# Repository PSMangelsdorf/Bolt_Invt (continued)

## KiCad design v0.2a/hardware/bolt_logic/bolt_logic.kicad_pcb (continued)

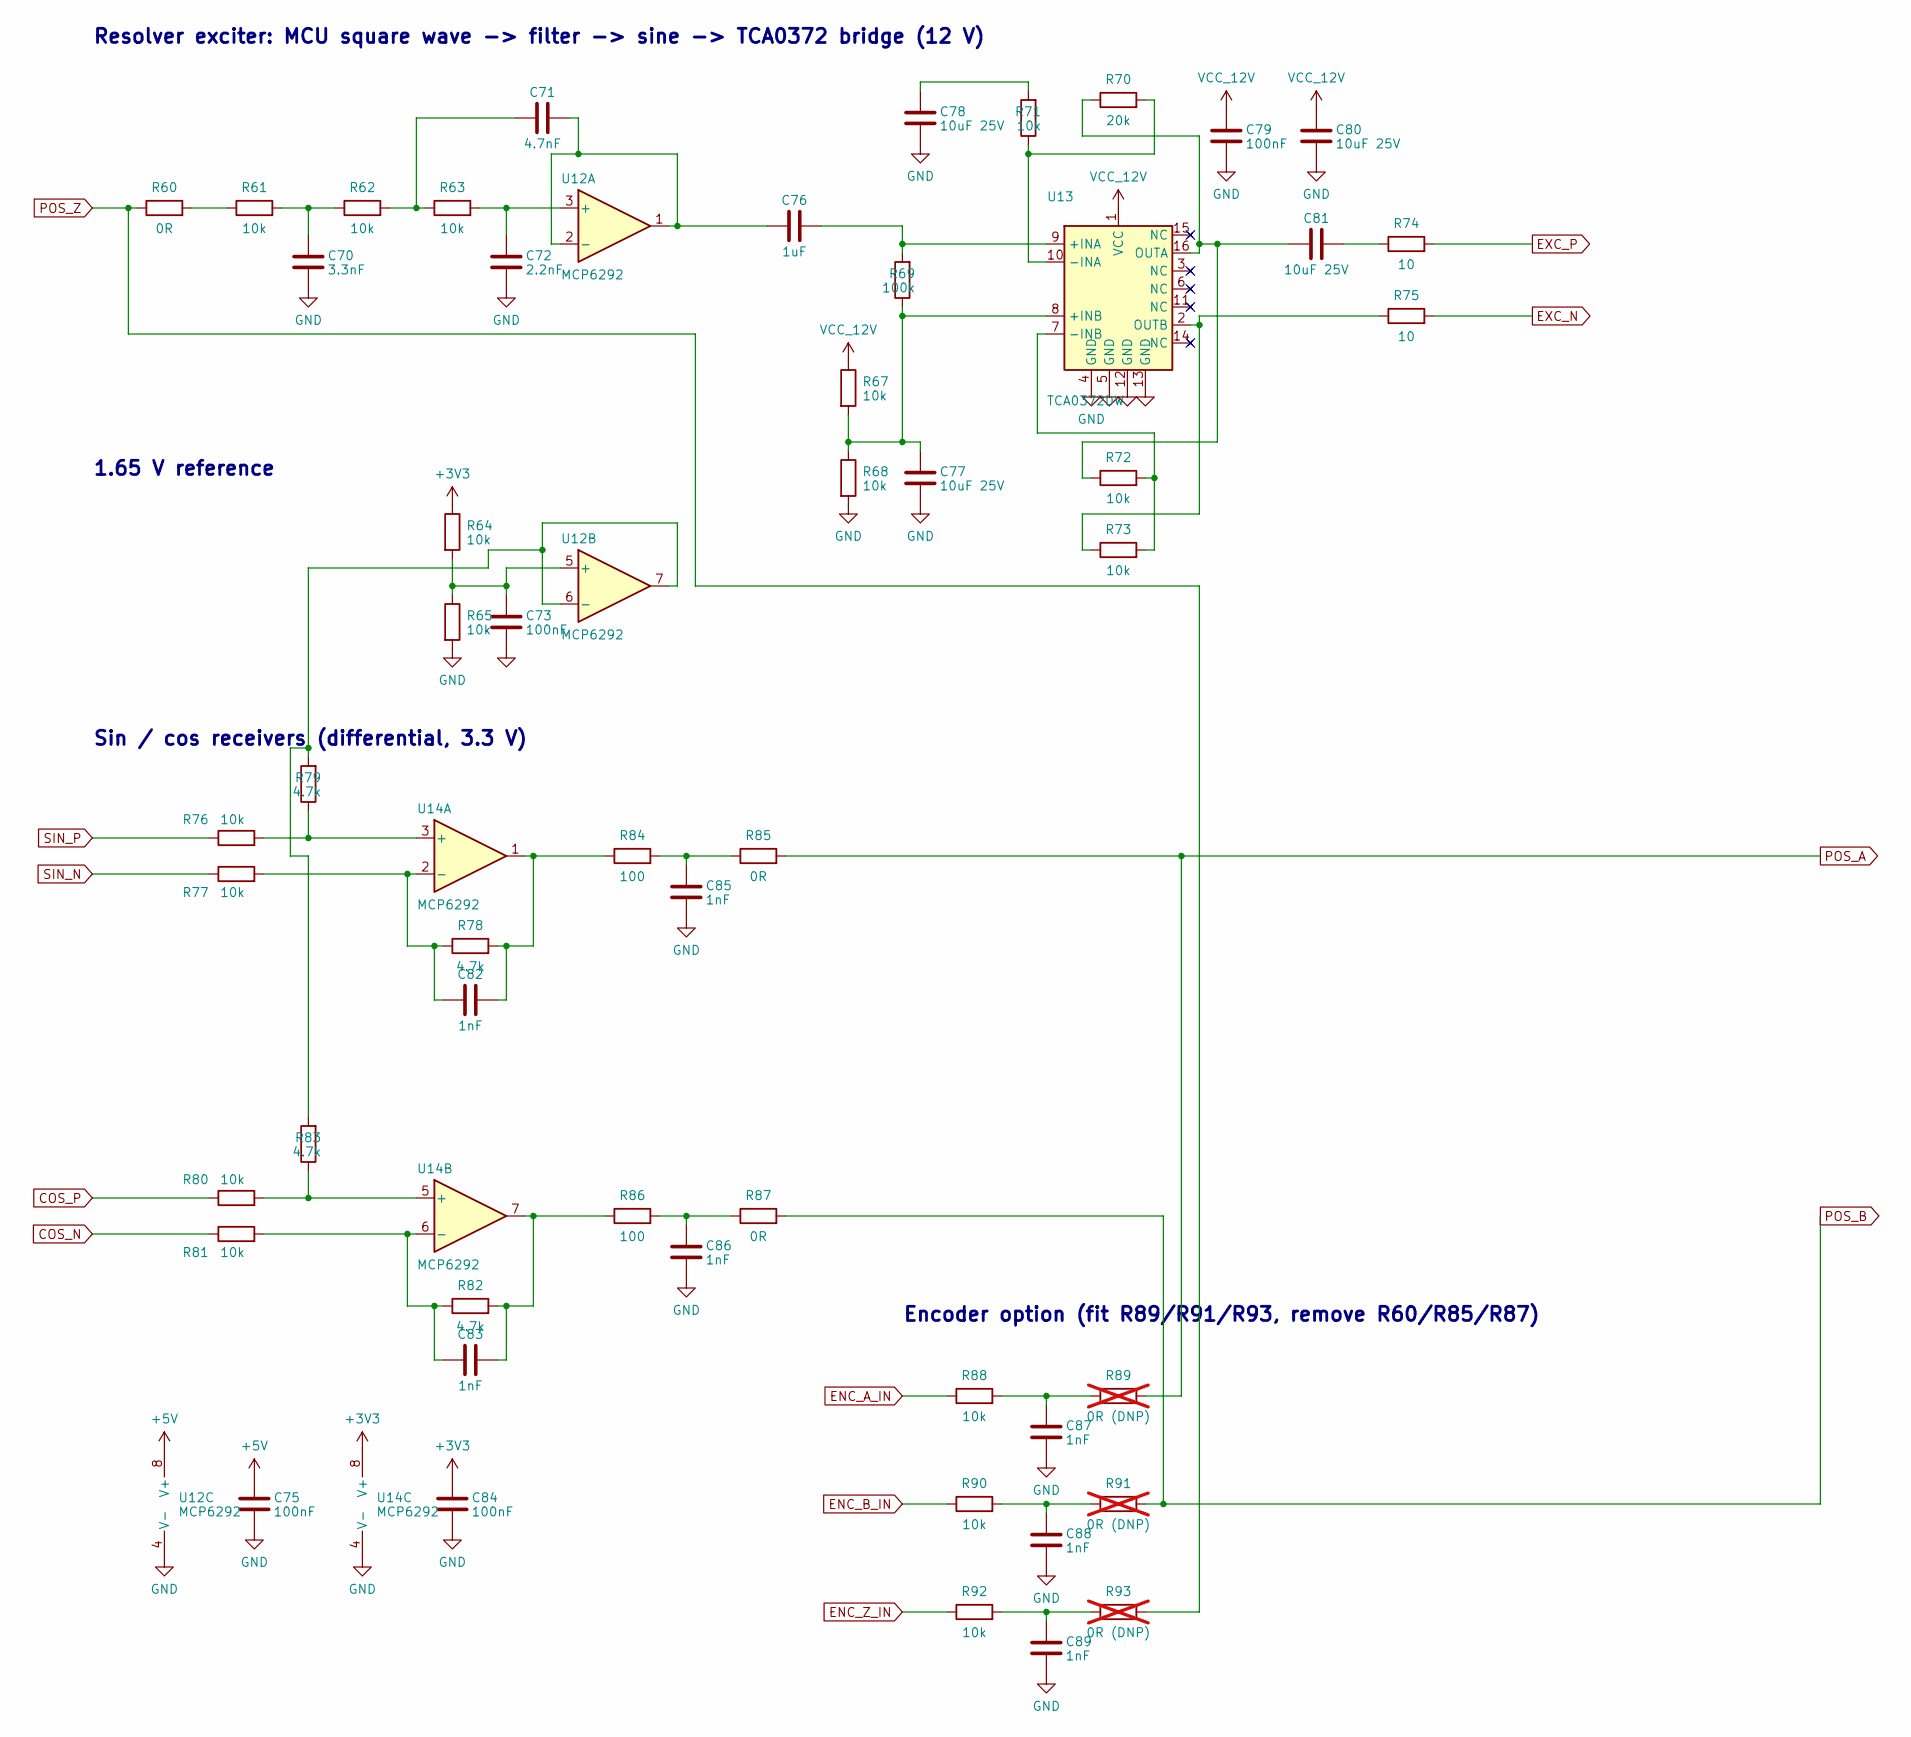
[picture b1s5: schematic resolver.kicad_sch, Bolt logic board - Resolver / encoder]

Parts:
C70: 3.3nF; C_0805_2012Metric
C71: 4.7nF; C_0805_2012Metric
C72: 2.2nF; C_0805_2012Metric
C73, C75, C79, C84: 100nF; C_0805_2012Metric
C76: 1uF; C_0805_2012Metric
C77, C78, C80, C81: 10uF 25V; C_1206_3216Metric
C82, C83, C85, C86, C87, C88, C89: 1nF; C_0805_2012Metric
R60, R85, R87: 0R; R_0805_2012Metric
R61, R62, R63, R64, R65, R67, R68, R71, R72, R73, R76, R77, R80, R81, R88, R90, R92: 10k; R_0805_2012Metric
R69: 100k; R_0805_2012Metric
R70: 20k; R_0805_2012Metric
R74, R75: 10; R_1206_3216Metric
R78, R79, R82, R83: 4.7k; R_0805_2012Metric
R84, R86: 100; R_0805_2012Metric
R89, R91, R93: 0R (DNP); R_0805_2012Metric; not fitted
U12, U14: MCP6292; SOIC-8_3.9x4.9mm_P1.27mm
U13: TCA0372DW; SOIC-16W_7.5x10.3mm_P1.27mm

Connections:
+3V3: C84.1, R64.1, U14.8 (V+); also elsewhere on the board
+5V: C75.1, U12.8 (V+); also elsewhere on the board
COS_INN: C83.1, R81.2, R82.1, U14.6 (-)
COS_INP: R80.2, R83.1, U14.5 (+)
COS_N: R81.1; also elsewhere on the board
COS_P: R80.1; also elsewhere on the board
ENC_A_F: C87.1, R88.2, R89.1
ENC_A_IN: R88.1; also elsewhere on the board
ENC_B_F: C88.1, R90.2, R91.1
ENC_B_IN: R90.1; also elsewhere on the board
ENC_Z_F: C89.1, R92.2, R93.1
ENC_Z_IN: R92.1; also elsewhere on the board
EXC_AC: C76.2, R69.2, U13.9 (+INA)
EXC_F1: C70.1, R61.2, R62.1
EXC_FBA: R70.2, R71.1, U13.10 (-INA)
EXC_FBB: R72.2, R73.2, U13.7 (-INB)
EXC_N: R75.2; also elsewhere on the board
EXC_OA: C81.1, R70.1, R72.1, U13.16 (OUTA)
EXC_OA_C: C81.2, R74.1
EXC_OB: R73.1, R75.1, U13.2 (OUTB)
EXC_P: R74.2; also elsewhere on the board
EXC_RGA: C78.1, R71.2
EXC_SIN: C71.2, C76.1, U12.1, U12.2 (-)
EXC_SK1: C71.1, R62.2, R63.1
EXC_SK2: C72.1, R63.2, U12.3 (+)
EXC_SQ: R60.2, R61.1
EXC_VB: C77.1, R67.2, R68.1, R69.1, U13.8 (+INB)
GND: C70.2, C72.2, C73.2, C75.2, C77.2, C78.2, C79.2, C80.2, C84.2, C85.2, C86.2, C87.2, C88.2, C89.2, R65.2, R68.2, U12.4 (V-), U13.4 (GND), U13.5 (GND), U13.12 (GND), U13.13 (GND), U14.4 (V-); also elsewhere on the board
POS_A: R85.2, R89.2; also elsewhere on the board
POS_B: R87.2, R91.2; also elsewhere on the board
POS_Z: R60.1, R93.2; also elsewhere on the board
RES_COS: C83.2, R82.2, R86.1, U14.7
RES_COS_F: C86.1, R86.2, R87.1
RES_SIN: C82.2, R78.2, R84.1, U14.1
RES_SIN_F: C85.1, R84.2, R85.1
SIN_INN: C82.1, R77.2, R78.1, U14.2 (-)
SIN_INP: R76.2, R79.1, U14.3 (+)
SIN_N: R77.1; also elsewhere on the board
SIN_P: R76.1; also elsewhere on the board
VCC_12V: C79.1, C80.1, R67.1, U13.1 (VCC); also elsewhere on the board
VREF_1V65: R79.2, R83.2, U12.6 (-), U12.7
VREF_DIV: C73.1, R64.2, R65.1, U12.5 (+)

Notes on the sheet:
Resolver exciter: MCU square wave -> filter -> sine -> TCA0372 bridge (12 V)
1.65 V reference
Sin / cos receivers (differential, 3.3 V)
Encoder option (fit R89/R91/R93, remove R60/R85/R87)

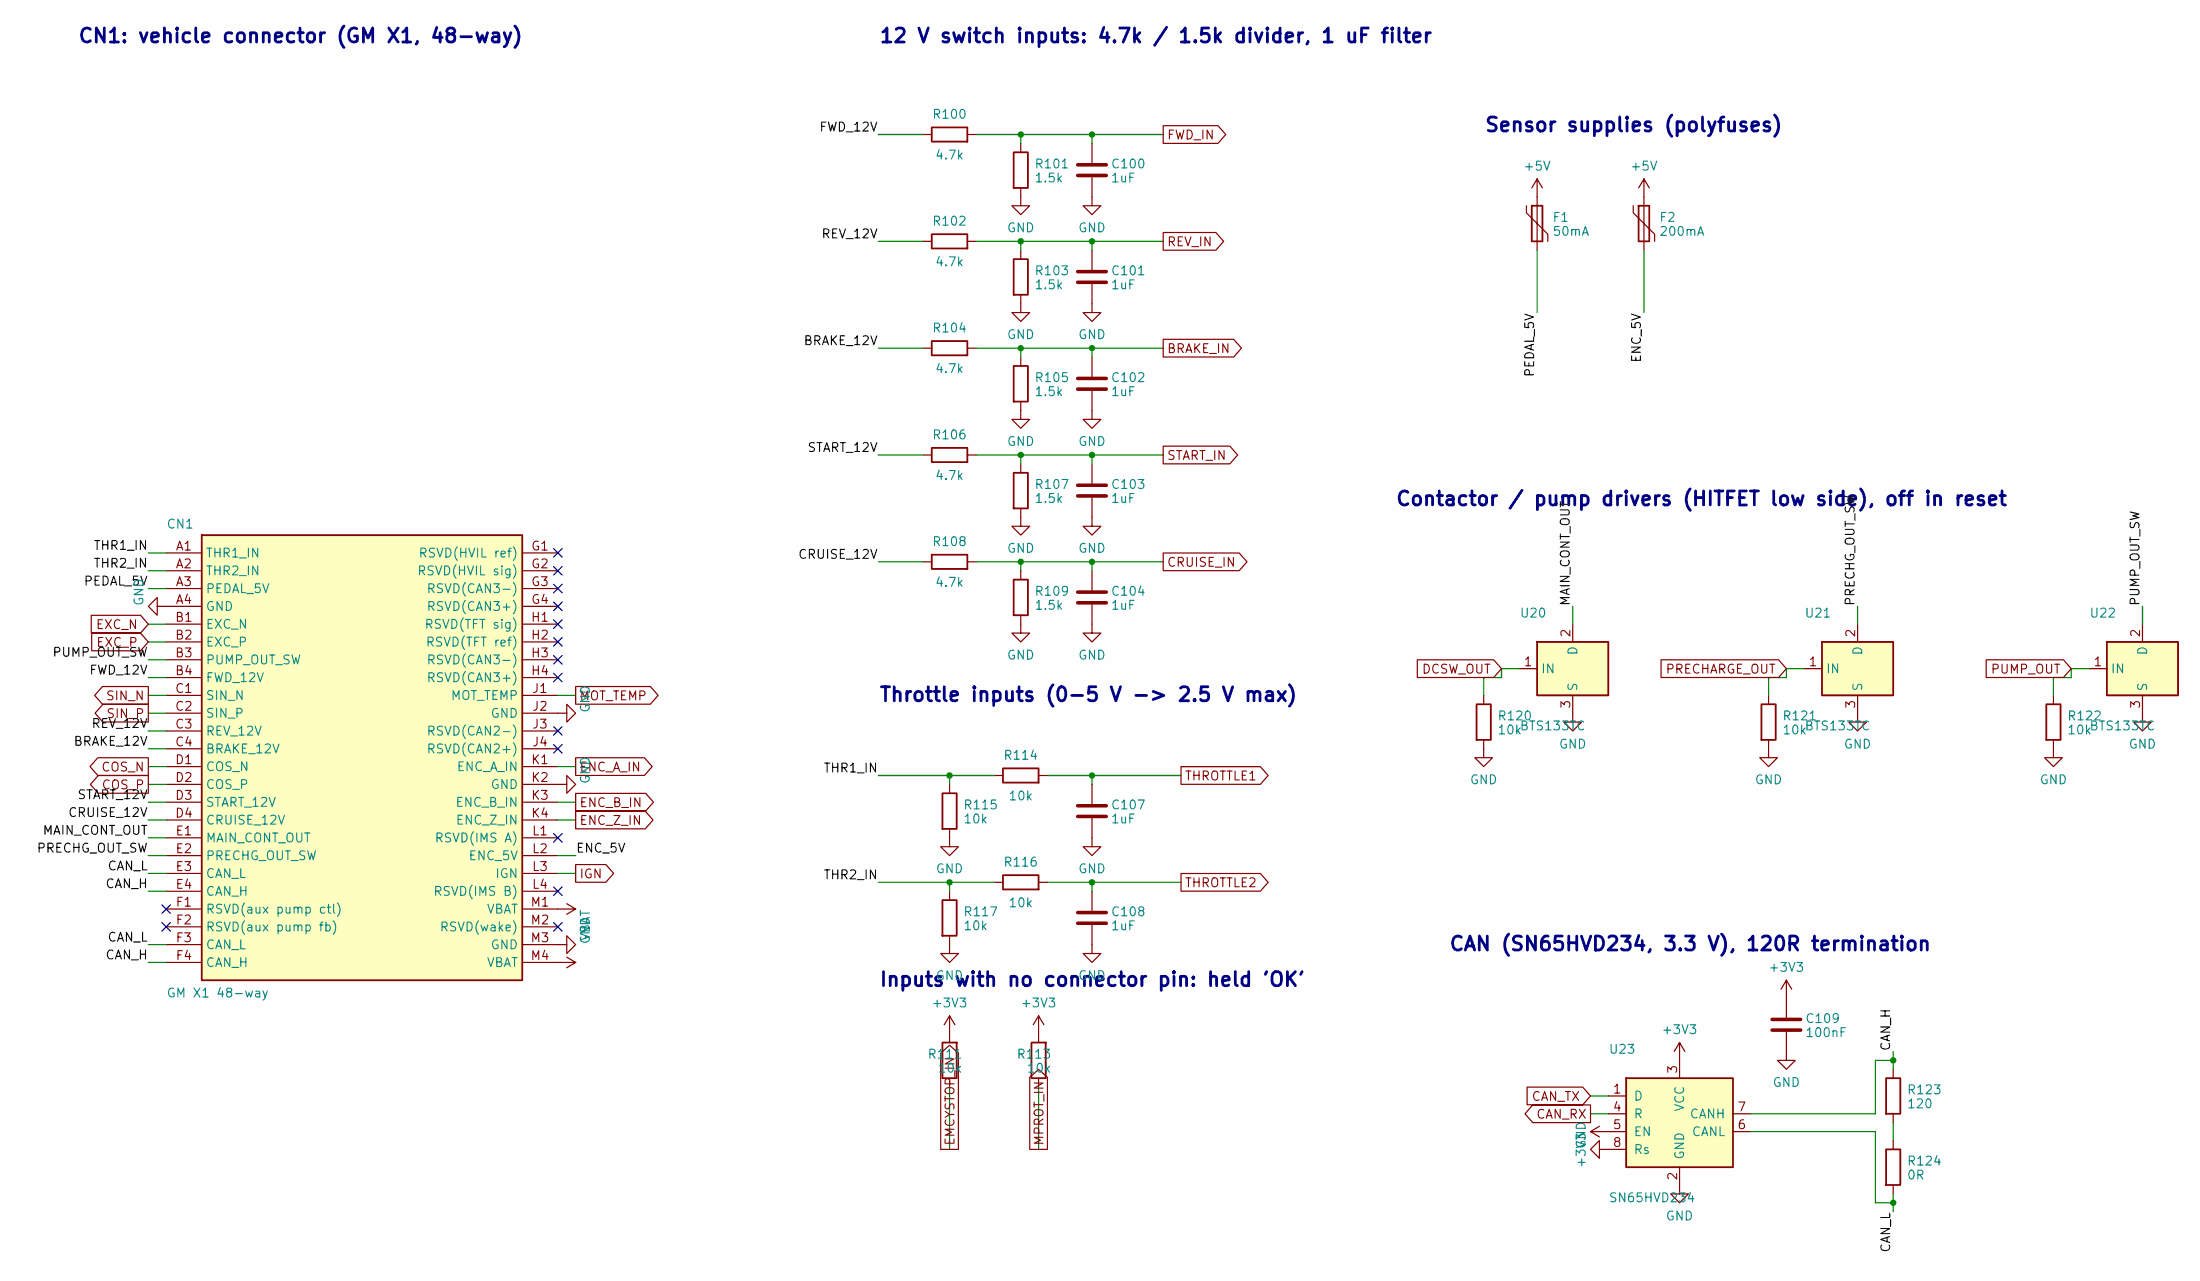
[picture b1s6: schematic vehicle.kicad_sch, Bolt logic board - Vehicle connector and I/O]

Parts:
C100, C101, C102, C103, C104, C107, C108: 1uF; C_0805_2012Metric
C109: 100nF; C_0805_2012Metric
CN1: GM X1 48-way; CN1_GM_48pos_4x12
F1: 50mA; Fuse_1206_3216Metric
F2: 200mA; Fuse_1206_3216Metric
R100, R102, R104, R106, R108: 4.7k; R_0805_2012Metric
R101, R103, R105, R107, R109: 1.5k; R_0805_2012Metric
R111, R113, R114, R115, R116, R117, R120, R121, R122: 10k; R_0805_2012Metric
R123: 120; R_0805_2012Metric
R124: 0R; R_0805_2012Metric
U20, U21, U22: BTS133TC; TO-263-2
U23: SN65HVD234; SOIC-8_3.9x4.9mm_P1.27mm

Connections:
+3V3: C109.1, R111.2, R113.2, U23.3 (VCC), U23.5 (EN); also elsewhere on the board
+5V: F1.1, F2.1; also elsewhere on the board
BRAKE_12V: CN1.C4 (BRAKE_12V), R104.1
BRAKE_IN: C102.1, R104.2, R105.1; also elsewhere on the board
CAN_H: CN1.E4 (CAN_H), CN1.F4 (CAN_H), R123.1, U23.7 (CANH)
CAN_L: CN1.E3 (CAN_L), CN1.F3 (CAN_L), R124.2, U23.6 (CANL)
CAN_RX: U23.4 (R); also elsewhere on the board
CAN_TERM: R123.2, R124.1
CAN_TX: U23.1 (D); also elsewhere on the board
COS_N: CN1.D1 (COS_N); also elsewhere on the board
COS_P: CN1.D2 (COS_P); also elsewhere on the board
CRUISE_12V: CN1.D4 (CRUISE_12V), R108.1
CRUISE_IN: C104.1, R108.2, R109.1; also elsewhere on the board
DCSW_OUT: R120.1, U20.1 (IN); also elsewhere on the board
EMCYSTOP_IN: R111.1; also elsewhere on the board
ENC_5V: CN1.L2 (ENC_5V), F2.2
ENC_A_IN: CN1.K1 (ENC_A_IN); also elsewhere on the board
ENC_B_IN: CN1.K3 (ENC_B_IN); also elsewhere on the board
ENC_Z_IN: CN1.K4 (ENC_Z_IN); also elsewhere on the board
EXC_N: CN1.B1 (EXC_N); also elsewhere on the board
EXC_P: CN1.B2 (EXC_P); also elsewhere on the board
FWD_12V: CN1.B4 (FWD_12V), R100.1
FWD_IN: C100.1, R100.2, R101.1; also elsewhere on the board
GND: C100.2, C101.2, C102.2, C103.2, C104.2, C107.2, C108.2, C109.2, CN1.A4 (GND), CN1.J2 (GND), CN1.K2 (GND), CN1.M3 (GND), R101.2, R103.2, R105.2, R107.2, R109.2, R115.2, R117.2, R120.2, R121.2, R122.2, U20.3 (S), U21.3 (S), U22.3 (S), U23.2 (GND), U23.8 (Rs); also elsewhere on the board
IGN: CN1.L3 (IGN); also elsewhere on the board
MAIN_CONT_OUT: CN1.E1 (MAIN_CONT_OUT), U20.2 (D)
MOT_TEMP: CN1.J1 (MOT_TEMP); also elsewhere on the board
MPROT_IN: R113.1; also elsewhere on the board
PEDAL_5V: CN1.A3 (PEDAL_5V), F1.2
PRECHARGE_OUT: R121.1, U21.1 (IN); also elsewhere on the board
PRECHG_OUT_SW: CN1.E2 (PRECHG_OUT_SW), U21.2 (D)
PUMP_OUT: R122.1, U22.1 (IN); also elsewhere on the board
PUMP_OUT_SW: CN1.B3 (PUMP_OUT_SW), U22.2 (D)
REV_12V: CN1.C3 (REV_12V), R102.1
REV_IN: C101.1, R102.2, R103.1; also elsewhere on the board
SIN_N: CN1.C1 (SIN_N); also elsewhere on the board
SIN_P: CN1.C2 (SIN_P); also elsewhere on the board
START_12V: CN1.D3 (START_12V), R106.1
START_IN: C103.1, R106.2, R107.1; also elsewhere on the board
THR1_IN: CN1.A1 (THR1_IN), R114.1, R115.1
THR2_IN: CN1.A2 (THR2_IN), R116.1, R117.1
THROTTLE1: C107.1, R114.2; also elsewhere on the board
THROTTLE2: C108.1, R116.2; also elsewhere on the board
VBAT: CN1.M1 (VBAT), CN1.M4 (VBAT); also elsewhere on the board

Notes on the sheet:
CN1: vehicle connector (GM X1, 48-way)
12 V switch inputs: 4.7k / 1.5k divider, 1 uF filter
Throttle inputs (0-5 V -> 2.5 V max)
Inputs with no connector pin: held 'OK'
Sensor supplies (polyfuses)
Contactor / pump drivers (HITFET low side), off in reset
CAN (SN65HVD234, 3.3 V), 120R termination

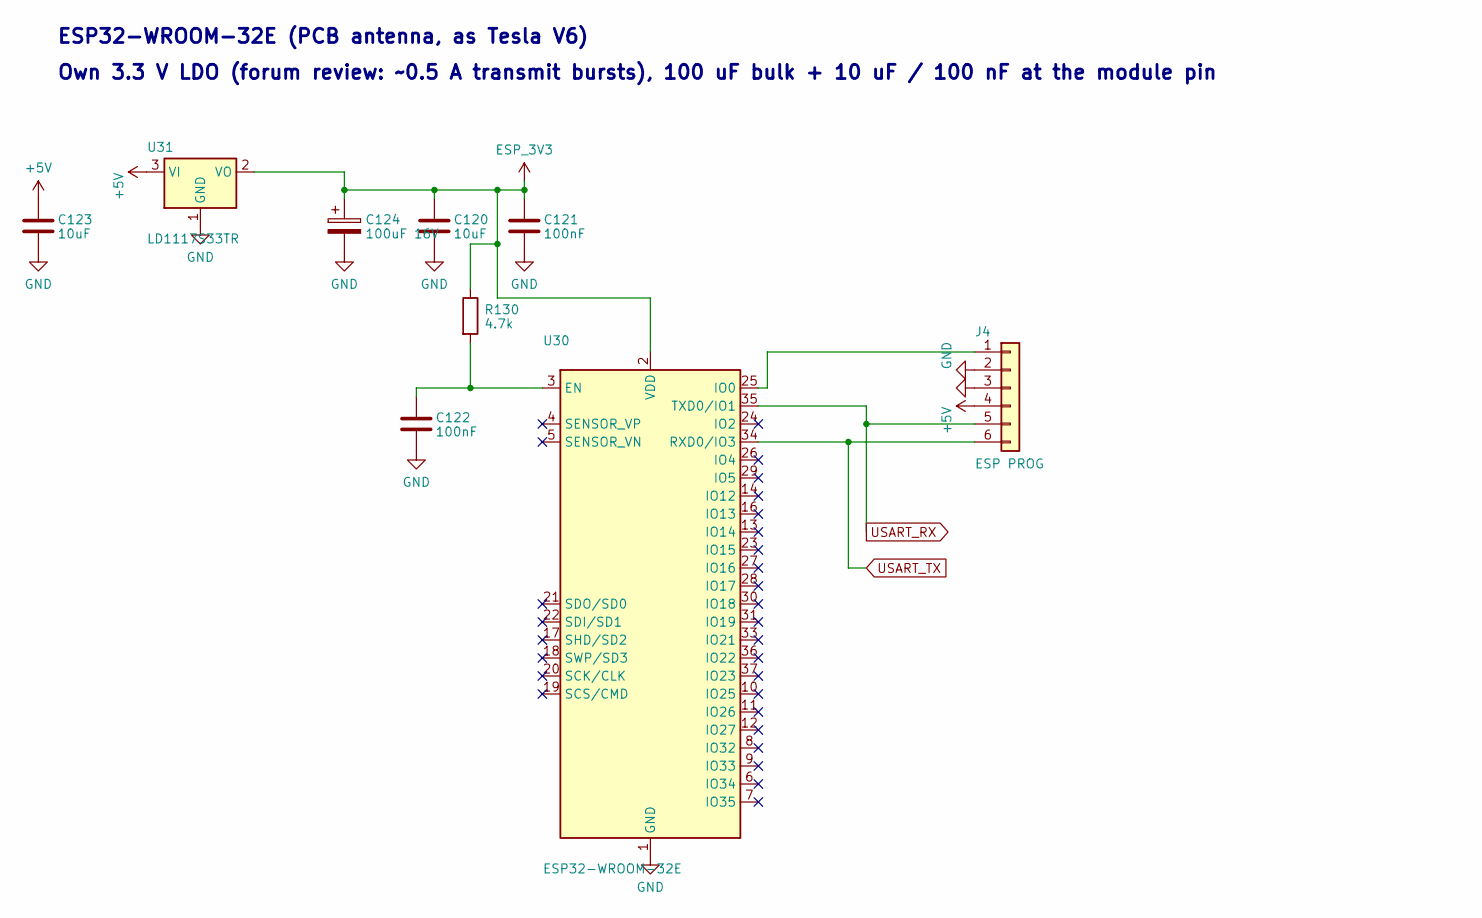
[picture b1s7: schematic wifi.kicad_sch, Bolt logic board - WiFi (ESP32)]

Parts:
C120, C123: 10uF; C_1206_3216Metric
C121, C122: 100nF; C_0805_2012Metric
C124: 100uF 16V; CP_Elec_6.3x5.4
J4: ESP PROG; PinHeader_1x06_P2.54mm_Vertical
R130: 4.7k; R_0805_2012Metric
U30: ESP32-WROOM-32E; ESP32-WROOM-32
U31: LD1117S33TR; SOT-223-3_TabPin2

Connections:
+5V: C123.1, J4.4, U31.3 (VI); also elsewhere on the board
ESP_3V3: C120.1, C121.1, C124.1, R130.1, U30.2 (VDD), U31.2 (VO)
ESP_EN: C122.1, R130.2, U30.3 (EN)
ESP_IO0: J4.1, U30.25 (IO0)
GND: C120.2, C121.2, C122.2, C123.2, C124.2, J4.2, J4.3, U30.1 (GND), U30.15 (GND), U30.38 (GND), U30.39 (GND), U31.1 (GND); also elsewhere on the board
USART_RX: J4.5, U30.35 (TXD0/IO1); also elsewhere on the board
USART_TX: J4.6, U30.34 (RXD0/IO3); also elsewhere on the board

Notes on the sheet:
ESP32-WROOM-32E (PCB antenna, as Tesla V6)
Own 3.3 V LDO (forum review: ~0.5 A transmit bursts), 100 uF bulk + 10 uF / 100 nF at the module pin

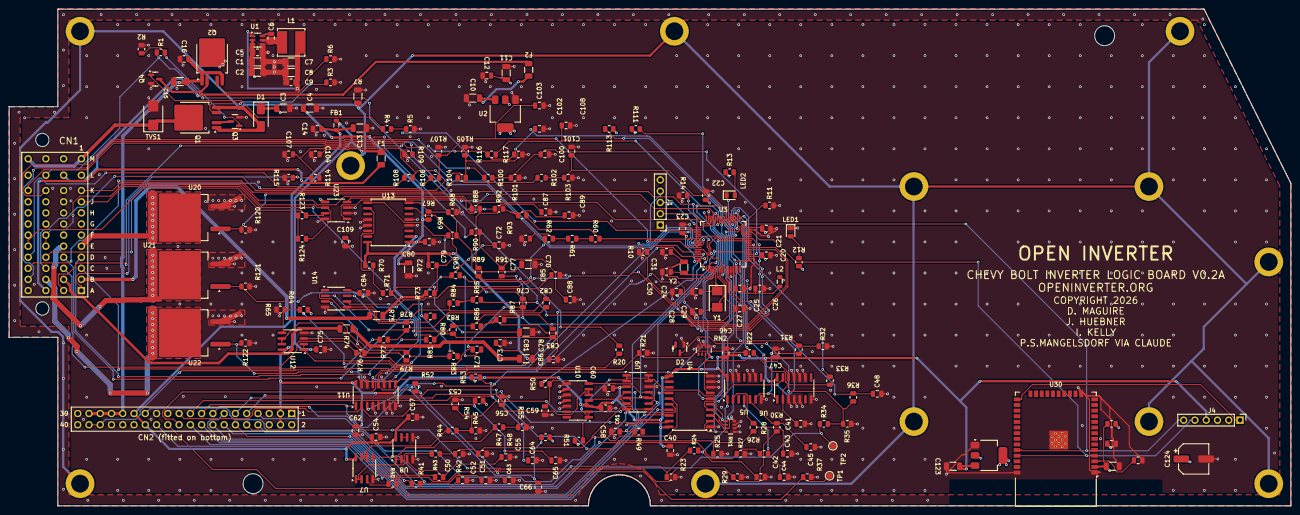
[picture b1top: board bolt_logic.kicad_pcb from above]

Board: 4 copper layers, 289.0 x 112.0 mm, 245 parts (1 on the bottom side), 162 nets.

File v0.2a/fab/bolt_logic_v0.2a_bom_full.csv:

Qty,Designators,Value,Footprint,Chosen spec,MPN,LCSC,Source,Fit by,Note
4,"C1,C2,C3,C4",10uF 50V,C_1206_3216Metric,10 uF X5R 50 V,CL31A106KBHNNNE,C13585,lcsc,smt,
27,"C5,C6,C9,C12,C14,C16,C20,C21,C22,C23,C26,C27,C40,C46,C47,C54,C57,C60,C61,C62,C73,C75,C79,C84,C109,C121,C122",100nF,C_0805_2012Metric,100 nF X7R 50 V,CC0805KRX7R9BB104,C49678,lcsc,smt,same part as V6; 50 V because some sit on 12 V rails
3,"C7,C8,C11",22uF,C_1206_3216Metric,22 uF X5R 25 V,CL31A226KAHNNNE,C12891,lcsc,smt,
4,"C10,C13,C120,C123",10uF,C_1206_3216Metric,10 uF X5R 25 V,CL31A106KAHNNNE,C9807,lcsc,smt,5 V / 3.3 V rails
5,"C15,C77,C78,C80,C81",10uF 25V,C_1206_3216Metric,10 uF X5R 25 V,CL31A106KAHNNNE,C9807,lcsc,smt,
1,C24,4.7uF,C_0805_2012Metric,4.7 uF X5R 25 V,CL21A475KAQNNNE,C1779,lcsc,smt,
15,"C25,C58,C59,C63,C64,C65,C66,C76,C100,C101,C102,C103,C104,C107,C108",1uF,C_0805_2012Metric,1 uF X7R 50 V,CL21B105KBFNNNE,C28323,lcsc,smt,same part as V6
2,"C28,C29",22pF,C_0805_2012Metric,22 pF C0G 50 V,0805CG220J500NT,C24658,lcsc,smt,
2,"C30,C31",10pF,C_0805_2012Metric,10 pF C0G 50 V,0805CG100J500NT,C157608,lcsc,smt,
5,"C41,C42,C43,C44,C45",10nF,C_0805_2012Metric,10 nF X7R 50 V,CL21B103KBANNNC,C1710,lcsc,smt,same part as V6
11,"C48,C51,C53,C56,C82,C83,C85,C86,C87,C88,C89",1nF,C_0805_2012Metric,1 nF X7R 50 V,CL21B102KBCNNNC,C46653,lcsc,smt,same part as V6
4,"C50,C52,C55,C71",4.7nF,C_0805_2012Metric,4.7 nF C0G 50 V (Murata),GRM2165C1H472JA01D,C77063,lcsc,smt,C0G proposed: exciter filter and current-sense filters
1,C70,3.3nF,C_0805_2012Metric,3.3 nF C0G 50 V (Murata),GRM2165C1H332JA01D,C77062,lcsc,smt,C0G proposed: exciter sine filter
1,C72,2.2nF,C_0805_2012Metric,2.2 nF C0G 50 V,0805CG222J500NT,C51795,lcsc,smt,C0G proposed: exciter sine filter
1,C124,100uF 16V,CP_Elec_6.3x5.4,"100 uF 16 V aluminium, 105 C, 6.3 x 5.4 mm (Nichicon WT)",UWT1C101MCL1GB,C340722,lcsc,smt,forum review (jrbe): >= 100 uF bulk at the ESP32 supply
1,CN1,GM X1 48-way,CN1_GM_48pos_4x12,vehicle connector,GM 48-way header (part not yet identified),,,hand,hand-solder (owner); 1.0 mm placeholder holes
1,CN2,SSW-120-01-T-D-LL,CN2_2x20_P2.54_Receptacle_Back,"2x20 receptacle, bottom side",SSW-120-01-T-D-LL (Samtec),,,hand,hand-solder (owner)
1,D1,SS54,D_SMA,40 V 5 A Schottky (MDD),SS54,C22452,lcsc,smt,same part as V6
1,D2,BAT54S,SOT-23,"dual Schottky, series (Nexperia)","BAT54S,215",C47546,lcsc,smt,
1,F1,50mA,Fuse_1206_3216Metric,"PPTC 50 mA hold, 60 V (Littelfuse)",1206L005/60WR,C315892,lcsc,smt,
1,F2,200mA,Fuse_1206_3216Metric,"PPTC 200 mA hold, 24 V (Littelfuse)",1206L020YR,C207035,lcsc,smt,
1,FB1,600R@100MHz 1A,L_0805_2012Metric,"600 ohm @ 100 MHz, 500 mA, 0.3 ohm",GZ2012D601TF,C1017,lcsc,smt,"rated 500 mA, not the 1 A in the value field; the +5V_A load (gate-board current sensors) is well under that"
1,J1,SWD,PinHeader_1x05_P2.54mm_Vertical,SWD,1x05 2.54 mm header,,,hand,hand-solder
1,J4,ESP PROG,PinHeader_1x06_P2.54mm_Vertical,ESP32 programming,1x06 2.54 mm header,,,hand,hand-solder
1,L1,6.8uH,L_Bourns_SRN6045TA,6.8 uH 20% (Bourns),SRN6045TA-6R8M,C2041457,lcsc,smt,
1,L2,10uH,L_0805_2012Metric,"10 uH 0805, DCR 0.3 ohm (TDK)",MLZ2012N100LT000,C88182,lcsc,smt,"L2 only (VDDA filter, a few mA). v0.2a: the ESP32 no longer runs through an inductor - it has its own LDO U31"
1,LED1,PWR green,LED_0805_2012Metric,green 0805,KT-0805G,C2297,lcsc,smt,
1,LED2,STATUS,LED_0805_2012Metric,green 0805,KT-0805G,C2297,lcsc,smt,colour not specified; green proposed
2,"Q1,Q2",BTS6143D,TO-252-4,"PROFET high-side 10 mohm, PG-TO252-5-11 (Infineon)",BTS6143D,C95232,lcsc,smt,owner: replaces BTS443P (same pinout and IN-to-GND input)
2,"Q3,Q4",2N7002,SOT-23,60 V N-MOSFET (JSCJ),2N7002,C8545,lcsc,smt,new in v0.1: BTS443P input switch
36,"R1,R5,R10,R14,R31,R35,R37,R49,R50,R51,R61,R62,R63,R64,R65,R67,R68,R71,R72,R73,R76,R77,R80,R81,R88,R90,R92,R111,R113,R114,R115,R116,R117,R120,R121,R122",10k,R_0805_2012Metric,10 k 1%,0805W8F1002T5E,C17414,lcsc,smt,
1,R2,6.8k,R_0805_2012Metric,6.8 k 1%,0805W8F6801T5E,C17772,lcsc,smt,
8,"R3,R4,R6,R13,R33,R40,R43,R46",1k,R_0805_2012Metric,1 k 1%,0805W8F1001T5E,C17513,lcsc,smt,
1,R7,0R,R_1206_3216Metric,0 ohm jumper 1206,1206W4F0000T5E,C17888,lcsc,smt,
17,"R11,R42,R45,R48,R52,R53,R54,R78,R79,R82,R83,R100,R102,R104,R106,R108,R130",4.7k,R_0805_2012Metric,4.7 k 1%,0805W8F4701T5E,C17673,lcsc,smt,
1,R12,470,R_0805_2012Metric,470 ohm 1%,0805W8F4700T5E,C17710,lcsc,smt,
1,R20,124k,R_0805_2012Metric,124 k 1% (Vishay),CRCW0805124KFKEA,C4135024,lcsc,smt,only 124 k 0805 found; check stock
6,"R21,R23,R25,R27,R29,R69",100k,R_0805_2012Metric,100 k 1%,0805W8F1003T5E,C149504,lcsc,smt,
5,"R22,R24,R26,R28,R30",560,R_0805_2012Metric,560 ohm 1%,0805W8F5600T5E,C28636,lcsc,smt,
2,"R32,R70",20k,R_0805_2012Metric,20 k 1%,0805W8F2002T5E,C4328,lcsc,smt,
1,R34,33k,R_0805_2012Metric,33 k 1%,0805W8F3302T5E,C17633,lcsc,smt,
1,R36,3.3k,R_0805_2012Metric,3.3 k 1%,0805W8F3301T5E,C26010,lcsc,smt,
3,"R41,R44,R47",2.7k,R_0805_2012Metric,2.7 k 1%,0805W8F2701T5E,C17530,lcsc,smt,
1,R55,2.2k,R_0805_2012Metric,2.2 k 1%,0805W8F2201T5E,C17520,lcsc,smt,
4,"R60,R85,R87,R124",0R,R_0805_2012Metric,0 ohm jumper,0805W8F0000T5E,C17477,lcsc,smt,
2,"R74,R75",10,R_1206_3216Metric,10 ohm 5% 1206,1206W4F100JT5E,C17903,lcsc,smt,
2,"R84,R86",100,R_0805_2012Metric,100 ohm 1%,0805W8F1000T5E,C17408,lcsc,smt,
3,"R89,R91,R93",0R (DNP),R_0805_2012Metric,not fitted,,,,none,DNP
5,"R101,R103,R105,R107,R109",1.5k,R_0805_2012Metric,1.5 k 1%,0805W8F1501T5E,C4310,lcsc,smt,
1,R123,120,R_0805_2012Metric,120 ohm 1% (CAN termination),0805W8F1200T5E,C17437,lcsc,smt,
2,"RN1,RN2",4x10k,R_Array_Convex_4x0603,4 x 10 k convex array,4D03WGJ0103T5E,C29718,lcsc,smt,same part as V6
1,TP1,GB_AUX,TestPoint_Pad_D1.5mm,test pad,,,,none,
1,TP2,GB_UDC,TestPoint_Pad_D1.5mm,test pad,,,,none,
1,TVS1,SMBJ26CA,D_SMB,"26 V bidirectional TVS, 600 W (Littelfuse)",SMBJ26CA,C83332,lcsc,smt,owner: Littelfuse instead of Bourns C3719606 (out of stock at JLCPCB)
1,U1,AP63205WU,TSOT-23-6,5 V 2 A sync buck (Diodes),AP63205WU-7,C2071056,lcsc,smt,
2,"U2,U31",LD1117S33TR,SOT-223-3_TabPin2,3.3 V LDO (ST),LD1117S33TR,C86781,lcsc,smt,
1,U3,STM32F103RBT6,LQFP-64_10x10mm_P0.5mm,MCU,STM32F103RBT6,C8735,lcsc,smt,same part as V6
1,U4,74HCT573,SOIC-20W_7.5x12.8mm_P1.27mm,octal latch (Nexperia),"74HCT573D,653",C5209384,lcsc,smt,"V6 BOM lists C5608, which LCSC shows as the HC part"
1,U5,74HC21,SOIC-14_3.9x8.7mm_P1.27mm,dual 4-input AND (Nexperia),"74HC21D,653",C5617,lcsc,smt,
1,U6,SN74ACT10,SOIC-14_3.9x8.7mm_P1.27mm,"triple 3-input NAND, ACT (TI)",SN74ACT10DR,C2861739,lcsc,smt,"owner: replaces 74HCT10D C547236 (out of stock); TTL-level inputs like HCT; low stock (89 at LCSC, Oct 2026)"
4,"U7,U8,U12,U14",MCP6292,SOIC-8_3.9x4.9mm_P1.27mm,dual RRIO op-amp (Microchip),MCP6292-E/SN,C556929,lcsc,smt,low stock at LCSC (38 in October 2026; 4 per board)
2,"U9,U10",LM2901,SOIC-14_3.9x8.7mm_P1.27mm,quad comparator (TI),LM2901DR,C7932,lcsc,smt,
1,U11,74HCT4052,SOIC-16_3.9x9.9mm_P1.27mm,"dual 4:1 analog mux, HCT (TI)",CD74HCT4052M96,C469908,lcsc,smt,
1,U13,TCA0372DW,SOIC-16W_7.5x10.3mm_P1.27mm,dual 1 A power op-amp (onsemi),TCA0372DWR2G,C362060,lcsc,smt,owner: replaces L272D (not stocked)
3,"U20,U21,U22",BTS133TC,TO-263-2,"HITFET low-side, TO-263",BTS133TC (BTS133TCBUMA1),C2681318,v6,smt,"owner: keep. Number from the V6 BOM, not found at LCSC: if JLCPCB can't place it, hand-solder (Digi-Key / Farnell / RS)"
1,U23,SN65HVD234,SOIC-8_3.9x4.9mm_P1.27mm,3.3 V CAN transceiver (TI),SN65HVD234DR,C99818,lcsc,smt,
1,U30,ESP32-WROOM-32E,ESP32-WROOM-32,"WiFi module, PCB antenna",ESP32-WROOM-32E-N4,C701341,lcsc,smt,
1,Y1,8MHz,Crystal_SMD_5032-2Pin_5.0x3.2mm,8 MHz 5032 (YXC),X50328MSB2GI,C115962,lcsc,smt,same part as V6
1,Y2,32.768kHz,Crystal_SMD_3215-2Pin_3.2x1.5mm,"32.768 kHz, 12.5 pF (Epson)",Q13FC13500004,C32346,lcsc,smt,12.5 pF crystal with the board's 10 pF caps runs a little fast (RTC only); no 7 pF version found at LCSC

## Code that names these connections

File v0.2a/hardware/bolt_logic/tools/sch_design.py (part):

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pw.add("FB1", "Device:FerriteBead", "600R@100MHz 1A", "Inductor_SMD:L_0805_2012Metric", {1: "+5V", 2: "+5V_A"})
pw.c("C13", "10uF", "+5V_A", "GND", fp=C1206)
pw.c("C14", "100nF", "+5V_A", "GND")
# Q2: gate-board 12 V, MCU-controlled (PA15), default off
pw.add("Q2", "Power_Management:BTS443P", "BTS6143D", "Package_TO_SOT_SMD:TO-252-4",
       {1: "+12V_GATE", 2: "Q2_IN", 3: "VCC_12V", 4: "Q2_IS"})
# Q4 pulls Q2's IN low when PA15 is high (same active-low input as Q1). R5 holds the gate
# below the 2N7002 threshold while PA15 is still JTDI with its internal pull-up at reset.
pw.r("R4", "1k", "GATE_PWR_EN", "Q2_G")
pw.r("R5", "10k", "GATE_PWR_EN", "GND")
pw.add("Q4", "Transistor_FET:2N7002", "2N7002", "Package_TO_SOT_SMD:SOT-23", {1: "Q2_G", 2: "GND", 3: "Q2_IN"})
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mcu = Sheet("mcu", "mcu.kicad_sch", "MCU")
STM = "MCU_ST_STM32F1:STM32F103RBTx"
stm_pins = by_name(STM, {
    "VBAT": "+3V3", "PC13": "DCSW_OUT", "PC14": "OSC32_IN", "PC15": "OSC32_OUT", "PD0": "OSC_IN",
    "PD1": "OSC_OUT", "NRST": "NRST", "PC0": "THROTTLE2", "PC1": "THROTTLE1", "PC2": "TMPM",
    "PC3": "UDC", "VSSA": "GND", "VDDA": "VDDA", "PA0": "GATE_OK", "PA1": "OCUR_OK",
    "PA2": "BRAKE_IN", "PA3": "MPROT_IN", "PA4": "FWD_IN", "PA5": "IL1", "PA6": "POS_A",
    "PA7": "POS_B", "PC4": "TMPHS", "PC5": "NC", "PB0": "IL2", "PB1": "PRECHARGE_OUT",
    "PB2": "BOOT1", "PB10": "USART_TX", "PB11": "USART_RX", "PB12": "PWM_INHIBIT",
    "PB13": "PWM_UL_3V", "PB14": "PWM_VL_3V", "PB15": "PWM_WL_3V", "PC6": "REV_IN",
    "PC7": "EMCYSTOP_IN", "PC8": "MUX_S1", "PC9": "GATE_FLT_MCU", "PA8": "PWM_UH_3V",
    "PA9": "PWM_VH_3V", "PA10": "PWM_WH_3V", "PA11": "CAN_RX", "PA12": "CAN_TX", "PA13": "SWDIO",
    "PA14": "SWCLK", "PA15": "GATE_PWR_EN", "PC10": "MUX_S0", "PC11": "NC", "PC12": "LED_OUT",
    "PD2": "POS_Z", "PB3": "NC", "PB4": "BOARD_ID", "PB5": "CRUISE_IN", "PB6": "START_IN",
    "PB7": "OCURLIM_NEG_PWM", "BOOT0": "BOOT0", "PB8": "OCURLIM_POS_PWM", "PB9": "PUMP_OUT",
})
stm_pins.update({n: "GND" for n in ("18", "31", "47", "63")})
stm_pins.update({n: "+3V3" for n in ("19", "32", "48", "64")})
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mcu.c("C27", "100nF", "NRST", "GND")
mcu.r("R10", "10k", "BOOT0", "GND")
mcu.r("R11", "4.7k", "BOOT1", "GND")
mcu.add("Y1", "Device:Crystal", "8MHz", "Crystal:Crystal_SMD_5032-2Pin_5.0x3.2mm", {1: "OSC_IN", 2: "OSC_OUT"})
mcu.c("C28", "22pF", "OSC_IN", "GND")
mcu.c("C29", "22pF", "OSC_OUT", "GND")
mcu.add("Y2", "Device:Crystal", "32.768kHz", "Crystal:Crystal_SMD_3215-2Pin_3.2x1.5mm", {1: "OSC32_IN", 2: "OSC32_OUT"})
mcu.c("C30", "10pF", "OSC32_IN", "GND")
mcu.c("C31", "10pF", "OSC32_OUT", "GND")
mcu.add("LED1", "Device:LED", "PWR green", "LED_SMD:LED_0805_2012Metric", {1: "GND", 2: "LED1_A"})
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mcu.r("R13", "1k", "+3V3", "LED2_A")
mcu.add("J1", "Connector_Generic:Conn_01x05", "SWD", "Connector_PinHeader_2.54mm:PinHeader_1x05_P2.54mm_Vertical",
        {1: "+3V3", 2: "SWDIO", 3: "SWCLK", 4: "NRST", 5: "GND"})
mcu.r("R14", "10k", "BOARD_ID", "GND")          # HW_BOLT detection strap (PB4)
flag(mcu, 8, "VDDA")

# =========================================================================
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       {1: "GND", 2: "ESP_3V3", 3: "+5V"})
wf.c("C123", "10uF", "+5V", "GND", fp=C1206)      # U31 input
wf.add("C124", "Device:C_Polarized", "100uF 16V", "Capacitor_SMD:CP_Elec_6.3x5.4", {1: "ESP_3V3", 2: "GND"})
wf.c("C120", "10uF", "ESP_3V3", "GND", fp=C1206)  # at U30 pin 2
wf.c("C121", "100nF", "ESP_3V3", "GND")           # at U30 pin 2
wf.r("R130", "4.7k", "ESP_3V3", "ESP_EN")
wf.c("C122", "100nF", "ESP_EN", "GND")
wf.add("J4", "Connector_Generic:Conn_01x06", "ESP PROG", "Connector_PinHeader_2.54mm:PinHeader_1x06_P2.54mm_Vertical",
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
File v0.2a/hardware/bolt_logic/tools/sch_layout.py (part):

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    "_notes": [(20.32, 35.56, "Battery in: TVS first, ignition high-side switch Q1, reverse-polarity diode D1"),
               (101.6, 50.8, "12 V rail"), (165.1, 45.72, "5 V buck (AP63205, 3.8-32 V in)"),
               (254.0, 45.72, "3.3 V LDO (MCU, analog)"),
               (63.5, 104.14, "Gate-board 12 V, switched by the MCU (PA15)"),
               (210.82, 93.98, "Filtered 5 V for the current sensors"),
               (25.4, 154.94, "Mounting holes: chassis, tied to GND through R7")],
    "_flags": (38.1, 215.9),
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# ======================================================================== VEHICLE
PLACE["vehicle"] = {
    "_labelrefs": ["CN1"],
    "_label": {"CAN_H": "R123.1", "CAN_L": "R124.2"},
    "_anchors": {},
    "_notes": [(25.4, 38.1, "CN1: vehicle connector (GM X1, 48-way)"),
               (139.7, 38.1, "12 V switch inputs: 4.7k / 1.5k divider, 1 uF filter"),
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# ======================================================================== WIFI
PLACE["wifi"] = {
    "_wire": ["ESP_3V3"],
    "_label": {"ESP_3V3": "C121.1"},
    "_anchors": {"USART_TX": (233.68, 124.46, "right"), "USART_RX": (233.68, 119.38, "right")},
    "_notes": [(119.38, 50.8, "ESP32-WROOM-32E (PCB antenna, as Tesla V6)"),
               (119.38, 55.88, "Own 3.3 V LDO (forum review: ~0.5 A transmit bursts), 100 uF bulk + 10 uF / 100 nF at the module pin")],
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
